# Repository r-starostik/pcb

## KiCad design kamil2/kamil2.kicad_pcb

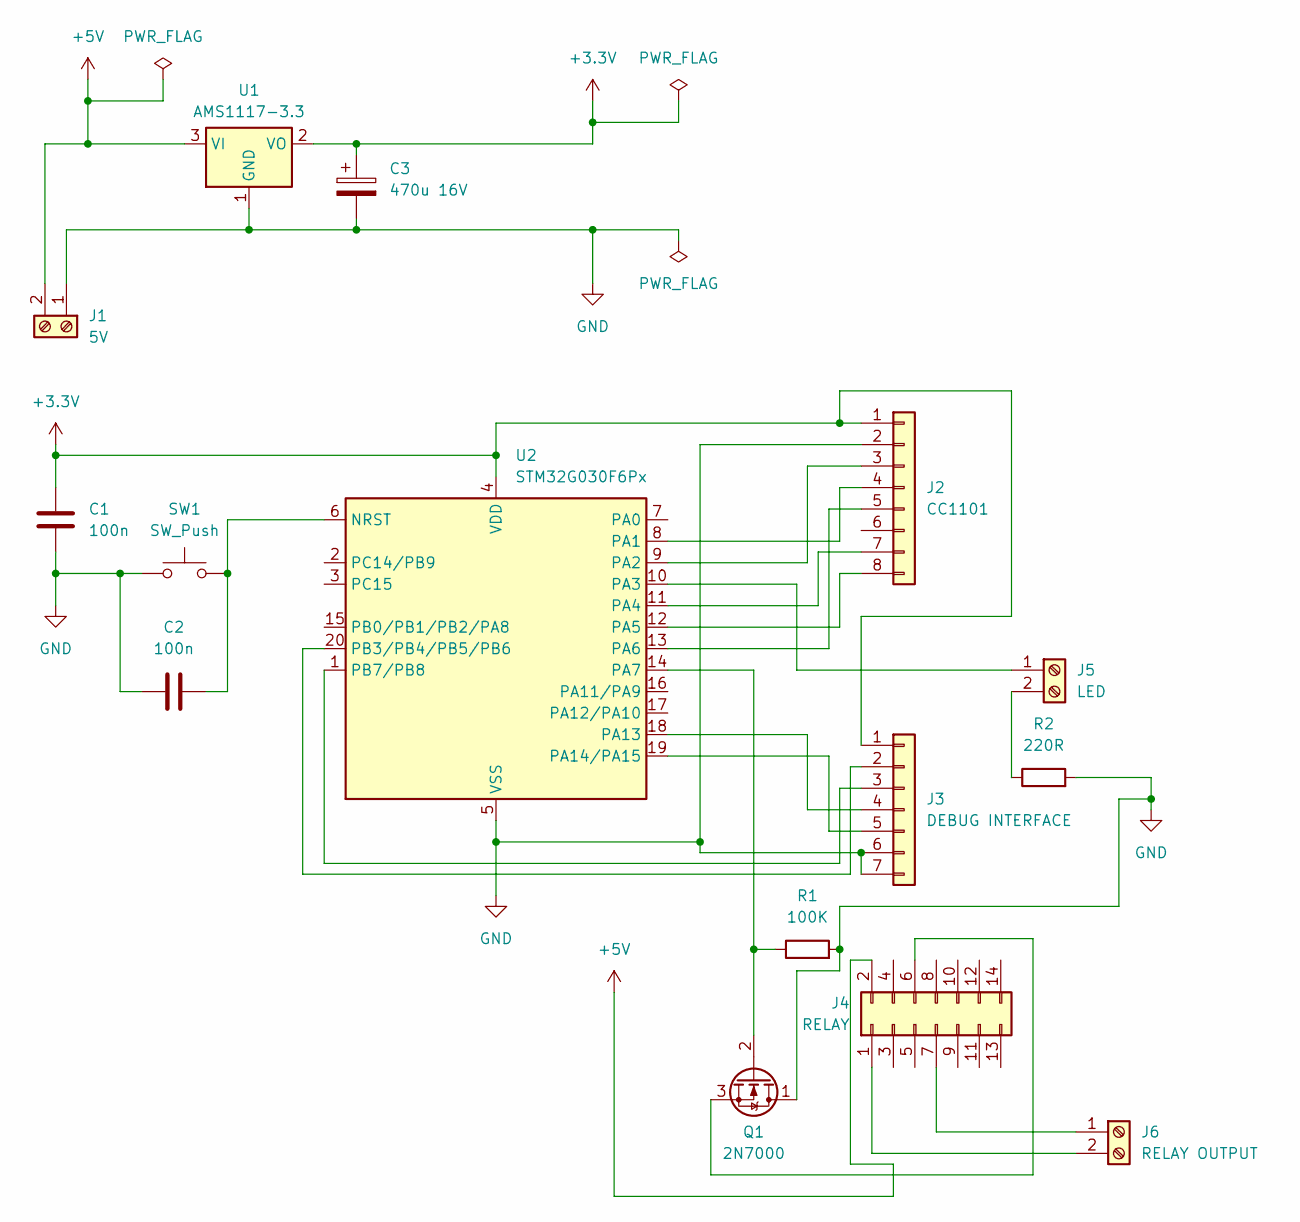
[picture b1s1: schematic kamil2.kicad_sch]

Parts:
C1, C2: 100n; C_1206_3216Metric
C3: 470u 16V; CP_Radial_D8.0mm_P3.80mm
J1: 5V; TerminalBlock_bornier-2_P5.08mm
J2: CC1101; PinSocket_1x08_P2.00mm_Vertical
J3: DEBUG INTERFACE; PinHeader_1x07_P2.54mm_Vertical
J4: RELAY; CERDIP-14_W7.62mm_SideBrazed
J5: LED; TerminalBlock_bornier-2_P5.08mm
J6: RELAY OUTPUT; TerminalBlock_bornier-2_P5.08mm
Q1: 2N7000; TO-92_Inline
R1: 100K; R_1206_3216Metric
R2: 220R; R_1206_3216Metric
SW1: SW_Push; SW_Tactile_SPST_NO_Straight_CK_PTS636Sx25SMTRLFS
U1: AMS1117-3.3; SOT-223-3_TabPin2
U2: STM32G030F6Px; TSSOP-20_4.4x6.5mm_P0.65mm

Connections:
+3.3V: C1.2, C3.1, J2.1, J3.1, U1.2 (VO), U2.4 (VDD)
+5V: J1.2, J4.2, U1.3 (VI)
GND: C1.1, C2.2, C3.2, J1.1, J2.2, J3.6, J3.7, Q1.1 (D), R1.2, R2.2, SW1.1, U1.1 (GND), U2.5 (VSS)
unnamed: J2.3, U2.9 (PA2)
unnamed: J2.4, U2.8 (PA1)
unnamed: J2.5, U2.13 (PA6)
unnamed: J2.7, U2.11 (PA4)
unnamed: J2.8, U2.12 (PA5)
unnamed: J3.2, U2.20 (PB3/PB4/PB5/PB6)
unnamed: J3.3, U2.1 (PB7/PB8)
unnamed: J3.4, U2.18 (PA13)
unnamed: J3.5, U2.19 (PA14/PA15)
unnamed: J4.1, J6.2
unnamed: J4.6, Q1.3 (S)
unnamed: J4.7, J6.1
unnamed: J5.1, U2.10 (PA3)
unnamed: J5.2, R2.1
unnamed: Q1.2 (G), R1.1, U2.14 (PA7)
unnamed: C2.1, SW1.2, U2.6 (NRST)

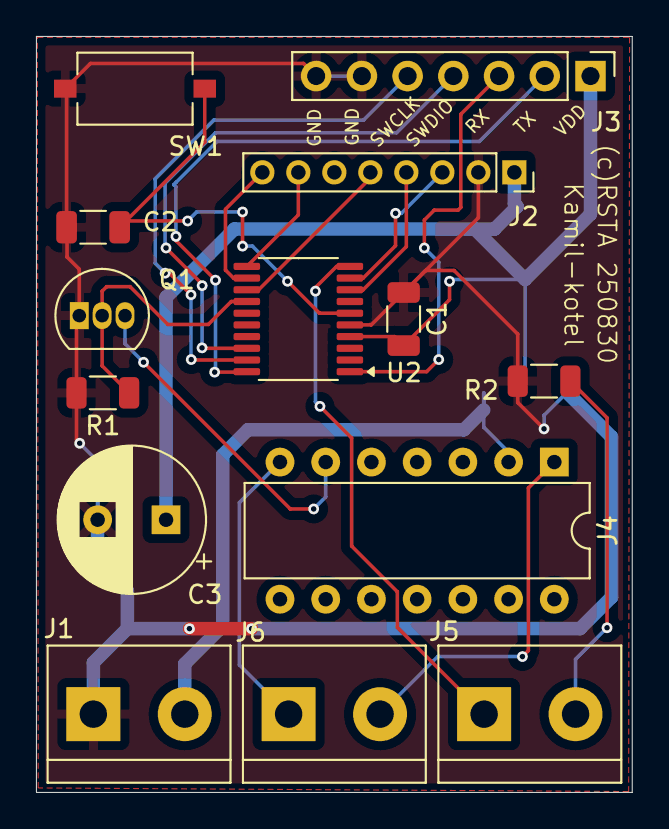
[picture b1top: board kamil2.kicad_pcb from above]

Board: 2 copper layers, 33.1 x 42.0 mm, 15 parts (1 on the bottom side), 19 nets.

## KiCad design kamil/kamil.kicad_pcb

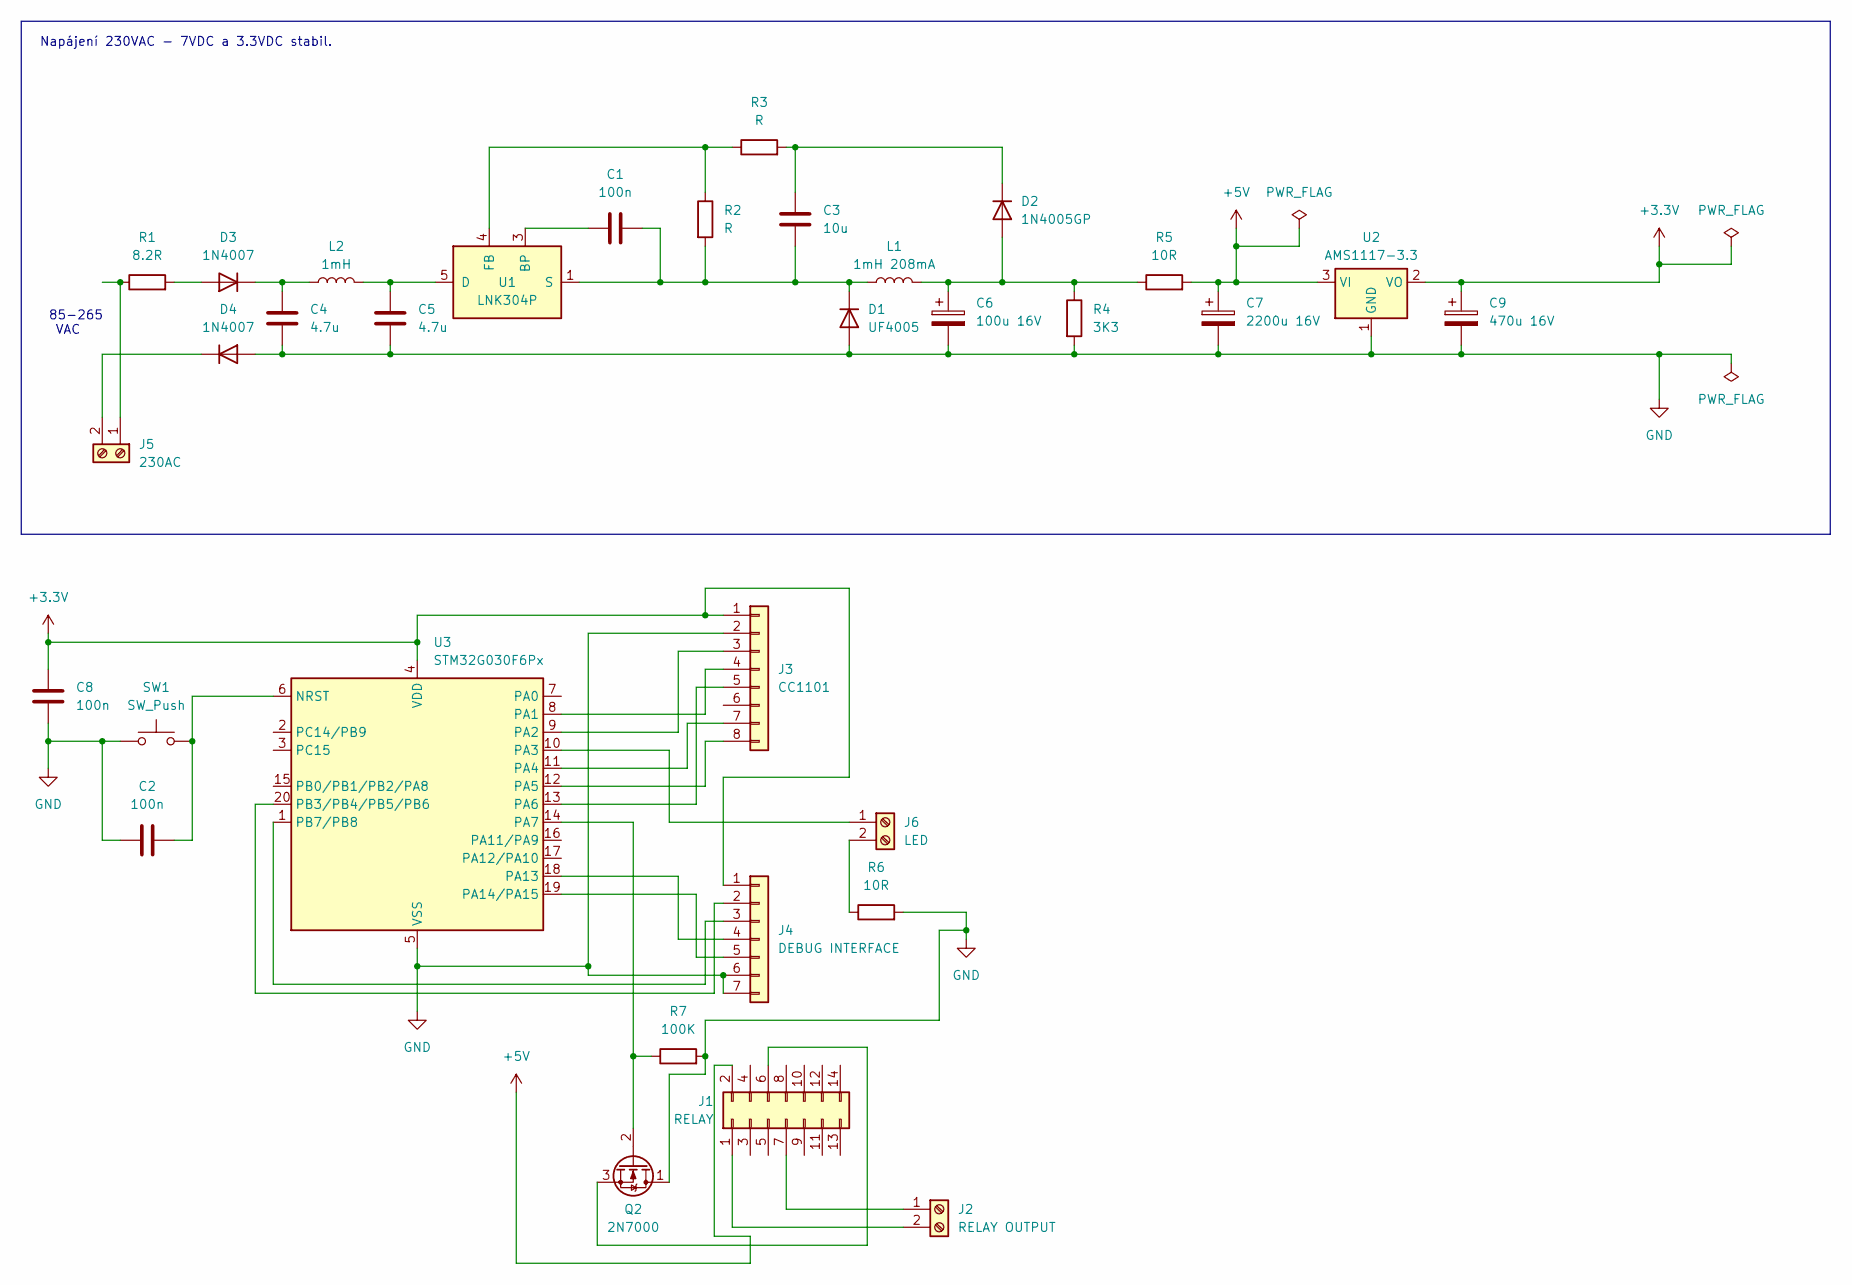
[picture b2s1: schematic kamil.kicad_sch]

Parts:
C1, C2, C8: 100n; C_1206_3216Metric
C3: 10u; CP_Radial_D5.0mm_P2.50mm
C4, C5: 4.7u; C_Rect_L29.0mm_W7.6mm_P27.50mm_MKT
C6: 100u 16V; CP_Radial_D5.0mm_P2.50mm
C7: 2200u 16V; CP_Radial_D12.5mm_P5.00mm
C9: 470u 16V; CP_Radial_D8.0mm_P3.80mm
D1: UF4005; D_DO-41_SOD81_P10.16mm_Horizontal
D2: 1N4005GP; D_DO-41_SOD81_P10.16mm_Horizontal
D3, D4: 1N4007; D_DO-41_SOD81_P10.16mm_Horizontal
J1: RELAY; CERDIP-14_W7.62mm_SideBrazed
J2: RELAY OUTPUT; TerminalBlock_bornier-2_P5.08mm
J3: CC1101; PinSocket_1x08_P2.00mm_Vertical
J4: DEBUG INTERFACE; PinHeader_1x07_P2.54mm_Vertical
J5: 230AC; TerminalBlock_bornier-2_P5.08mm
J6: LED; TerminalBlock_bornier-2_P5.08mm
L1: 1mH 208mA; L_Radial_D10.5mm_P5.00mm_Abacron_AISR-01
L2: 1mH; L_Radial_D10.5mm_P5.00mm_Abacron_AISR-01
Q2: 2N7000; TO-92_Inline
R1: 8.2R; R_Axial_DIN0414_L11.9mm_D4.5mm_P15.24mm_Horizontal
R2, R3: R; R_1206_3216Metric
R4: 3K3; R_1206_3216Metric
R5, R6: 10R; R_1206_3216Metric
R7: 100K; R_1206_3216Metric
SW1: SW_Push; SW_Tactile_SPST_NO_Straight_CK_PTS636Sx25SMTRLFS
U1: LNK304P; PowerIntegrations_PDIP-8B
U2: AMS1117-3.3; SOT-223-3_TabPin2
U3: STM32G030F6Px; TSSOP-20_4.4x6.5mm_P0.65mm

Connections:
+3.3V: C8.2, C9.1, J3.1, J4.1, U2.2 (VO), U3.4 (VDD)
+5V: C7.1, J1.2, R5.2, U2.3 (VI)
GND: C2.2, C4.2, C5.2, C6.2, C7.2, C8.1, C9.2, D1.2 (A), D4.2 (A), J3.2, J4.6, J4.7, Q2.1 (D), R4.2, R6.2, R7.2, SW1.1, U2.1 (GND), U3.5 (VSS)
unnamed: C1.2, C3.2, D1.1 (K), L1.1, R2.2, U1.1 (S), U1.2 (S), U1.7 (S), U1.8 (S)
unnamed: C6.1, D2.2 (A), L1.2, R4.1, R5.1
unnamed: C3.1, D2.1 (K), R3.2
unnamed: D3.2 (A), R1.2
unnamed: C4.1, D3.1 (K), L2.1
unnamed: D4.1 (K), J5.2
unnamed: J1.1, J2.2
unnamed: J1.6, Q2.3 (S)
unnamed: J1.7, J2.1
unnamed: J3.3, U3.9 (PA2)
unnamed: J3.4, U3.8 (PA1)
unnamed: J3.5, U3.13 (PA6)
unnamed: J3.7, U3.11 (PA4)
unnamed: J3.8, U3.12 (PA5)
unnamed: J4.2, U3.20 (PB3/PB4/PB5/PB6)
unnamed: J4.3, U3.1 (PB7/PB8)
unnamed: J4.4, U3.18 (PA13)
unnamed: J4.5, U3.19 (PA14/PA15)
unnamed: J5.1, R1.1
unnamed: J6.1, U3.10 (PA3)
unnamed: J6.2, R6.1
unnamed: Q2.2 (G), R7.1, U3.14 (PA7)
unnamed: C1.1, U1.3 (BP)
unnamed: C5.1, L2.2, U1.5 (D)
unnamed: R2.1, R3.1, U1.4 (FB)
unnamed: C2.1, SW1.2, U3.6 (NRST)

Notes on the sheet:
Napájení 230VAC - 7VDC a 3.3VDC stabil.
85-265 VAC

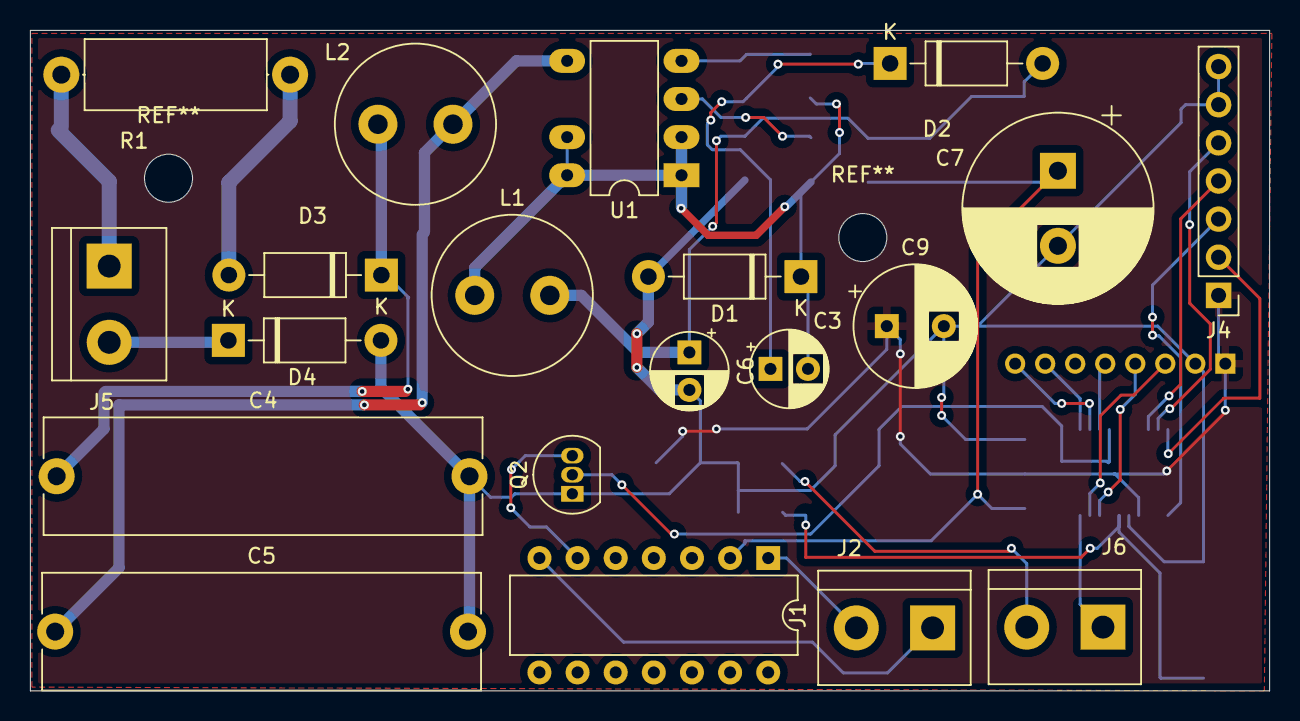
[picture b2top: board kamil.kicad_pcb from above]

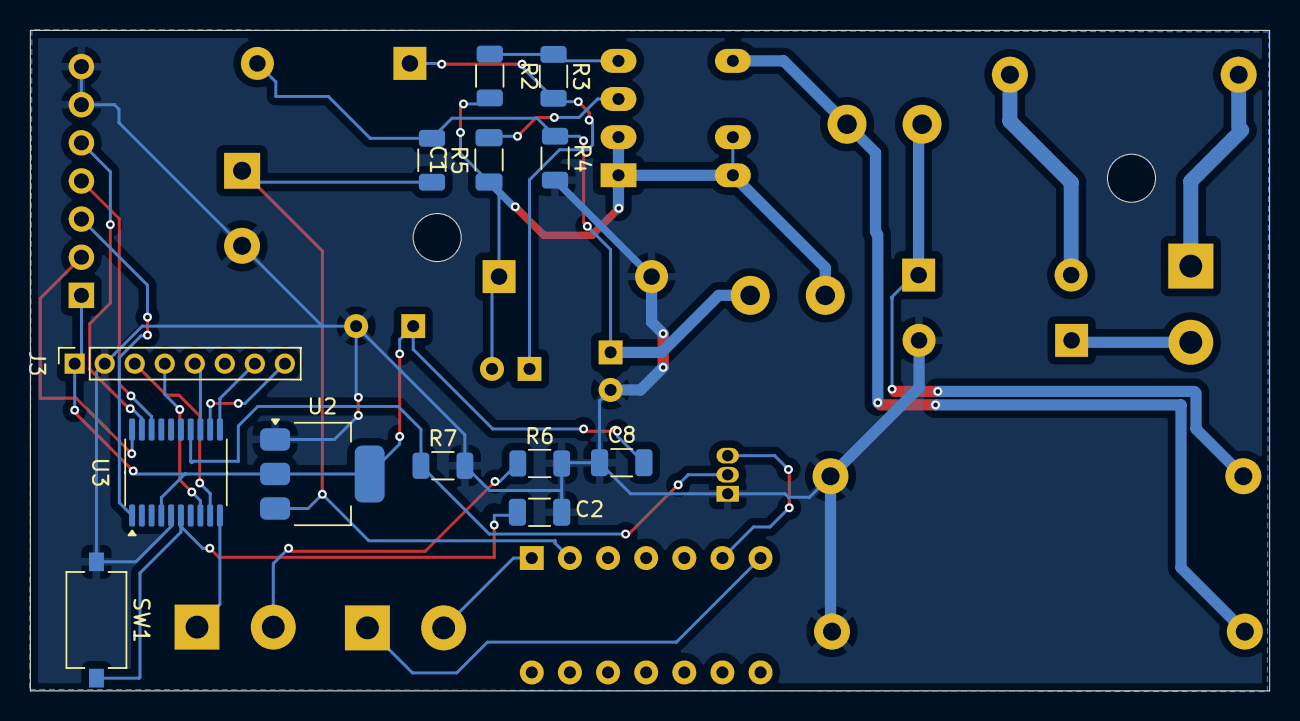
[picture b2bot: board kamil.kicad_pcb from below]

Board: 2 copper layers, 82.5 x 44.0 mm, 33 parts (13 on the bottom side), 29 nets.

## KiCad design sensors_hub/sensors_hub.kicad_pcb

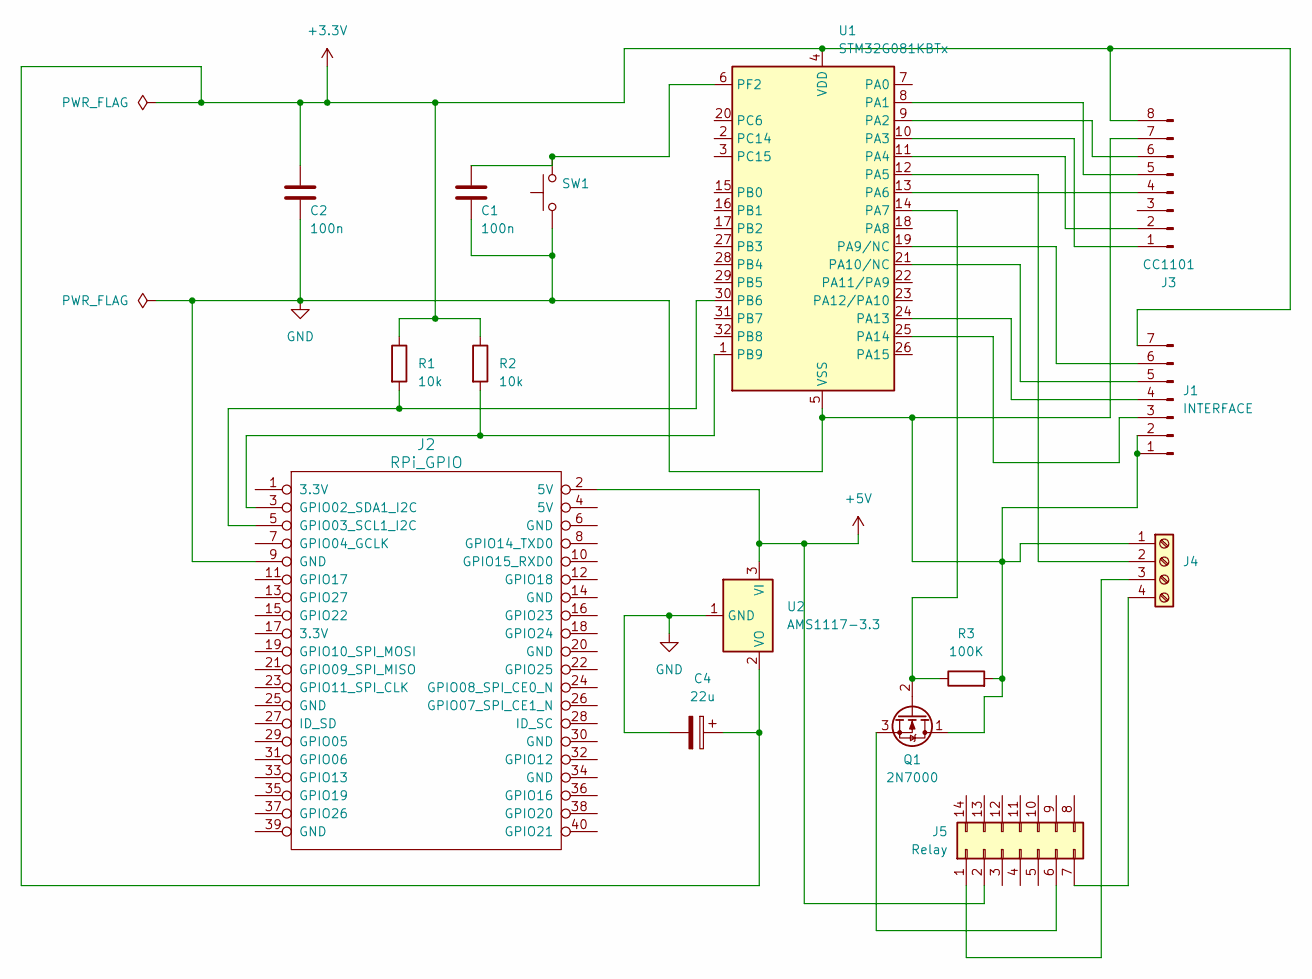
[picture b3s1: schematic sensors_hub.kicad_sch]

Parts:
C1: 100n; R_1206_3216Metric
C2: 100n; C_1206_3216Metric
C4: 22u; CP_Radial_D5.0mm_P2.00mm
J1: INTERFACE; PinHeader_1x07_P2.54mm_Vertical
J2: RPi_GPIO; PinSocket_2x20_P2.54mm_Vertical
J3: CC1101; PinSocket_1x08_P2.00mm_Vertical
J4: TerminalBlock_bornier-4_P5.08mm
J5: Relay; CERDIP-14_W7.62mm_SideBrazed
Q1: 2N7000; TO-92_Inline
R1, R2: 10k; R_1206_3216Metric
R3: 100K; R_1206_3216Metric
SW1: SW_Push; SW_Tactile_SPST_NO_Straight_CK_PTS636Sx25SMTRLFS
U1: STM32G081KBTx; LQFP-32_7x7mm_P0.8mm
U2: AMS1117-3.3; SOT-223-3_TabPin2

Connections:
+3.3V: C2.1, C4.1, J1.7, J3.8, R1.1, R2.1, U1.4 (VDD), U2.2 (VO)
+5V: J2.2 (5V), J5.2, U2.3 (VI)
GND: C1.2, C2.2, C4.2, J1.1, J1.2, J2.9 (GND), J3.7, J4.1, Q1.1 (D), R3.2, SW1.1, U1.5 (VSS), U2.1 (GND)
unnamed: J1.3, U1.25 (PA14)
unnamed: J1.4, U1.24 (PA13)
unnamed: J1.5, U1.21 (PA10/NC)
unnamed: J1.6, U1.19 (PA9/NC)
unnamed: J2.3 (GPIO02_SDA1_I2C), R2.2, U1.1 (PB9)
unnamed: J2.5 (GPIO03_SCL1_I2C), R1.2, U1.30 (PB6)
unnamed: J3.1, U1.10 (PA3)
unnamed: J3.2, U1.11 (PA4)
unnamed: J3.4, U1.13 (PA6)
unnamed: J3.5, U1.8 (PA1)
unnamed: J3.6, U1.9 (PA2)
unnamed: J4.2, U1.12 (PA5)
unnamed: J4.3, J5.1
unnamed: J4.4, J5.7
unnamed: J5.6, Q1.3 (S)
unnamed: Q1.2 (G), R3.1, U1.14 (PA7)
unnamed: C1.1, SW1.2, U1.6 (PF2)

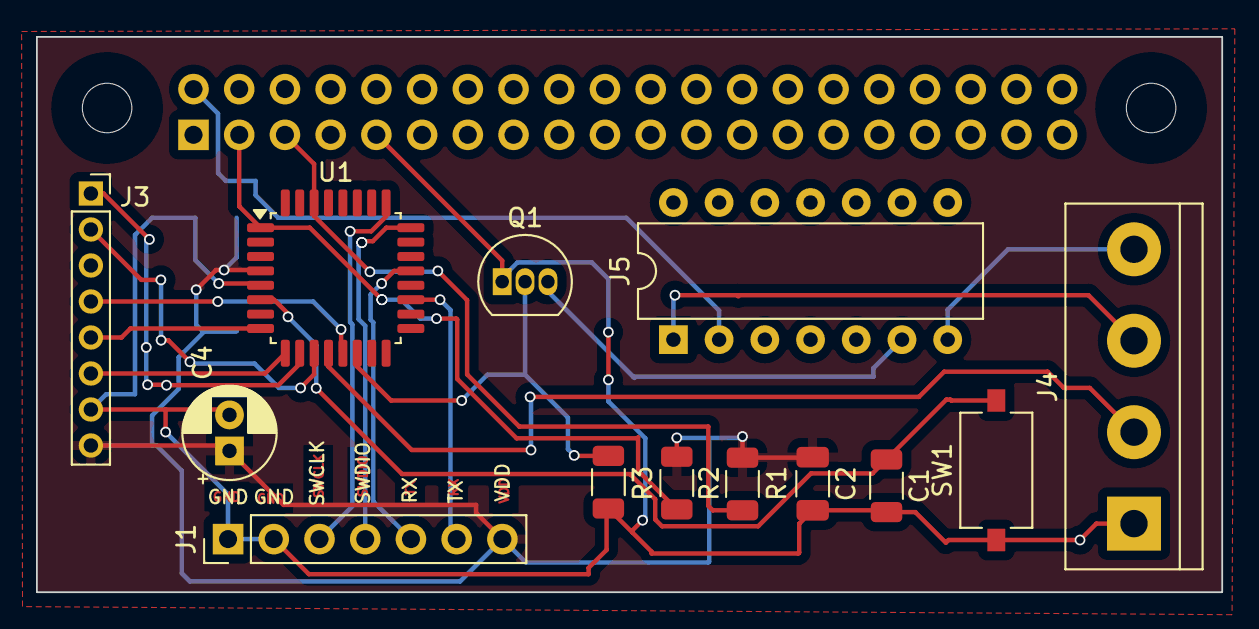
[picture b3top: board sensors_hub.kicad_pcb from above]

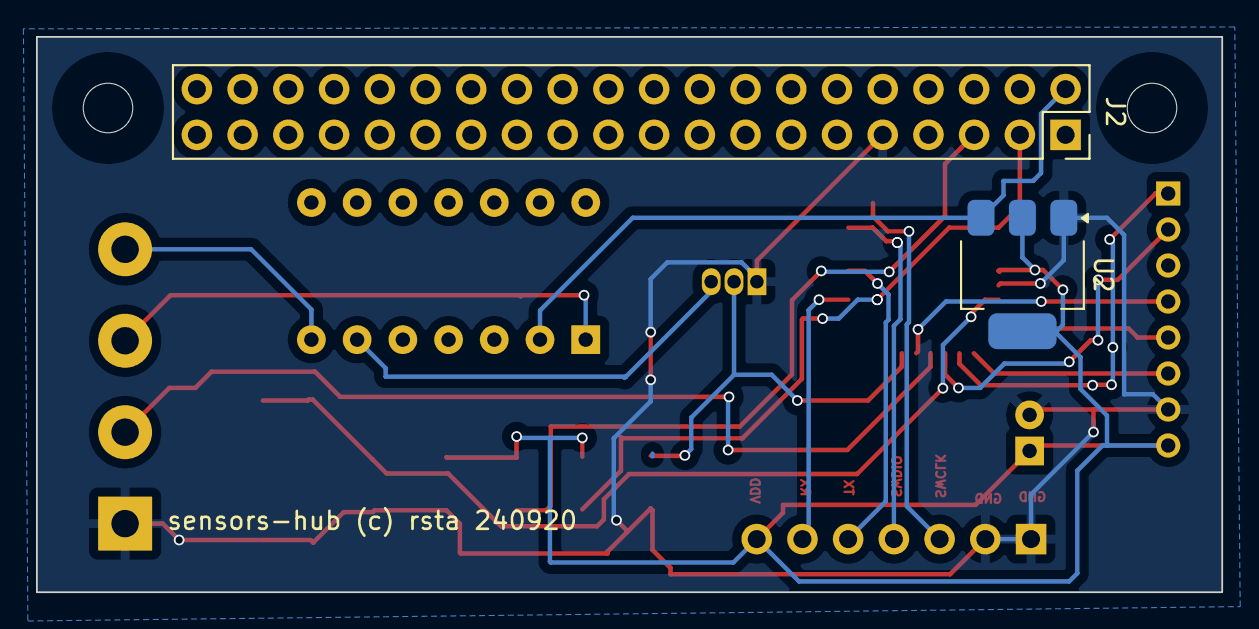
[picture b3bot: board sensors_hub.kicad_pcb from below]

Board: 2 copper layers, 65.9 x 30.8 mm, 15 parts (2 on the bottom side), 20 nets.

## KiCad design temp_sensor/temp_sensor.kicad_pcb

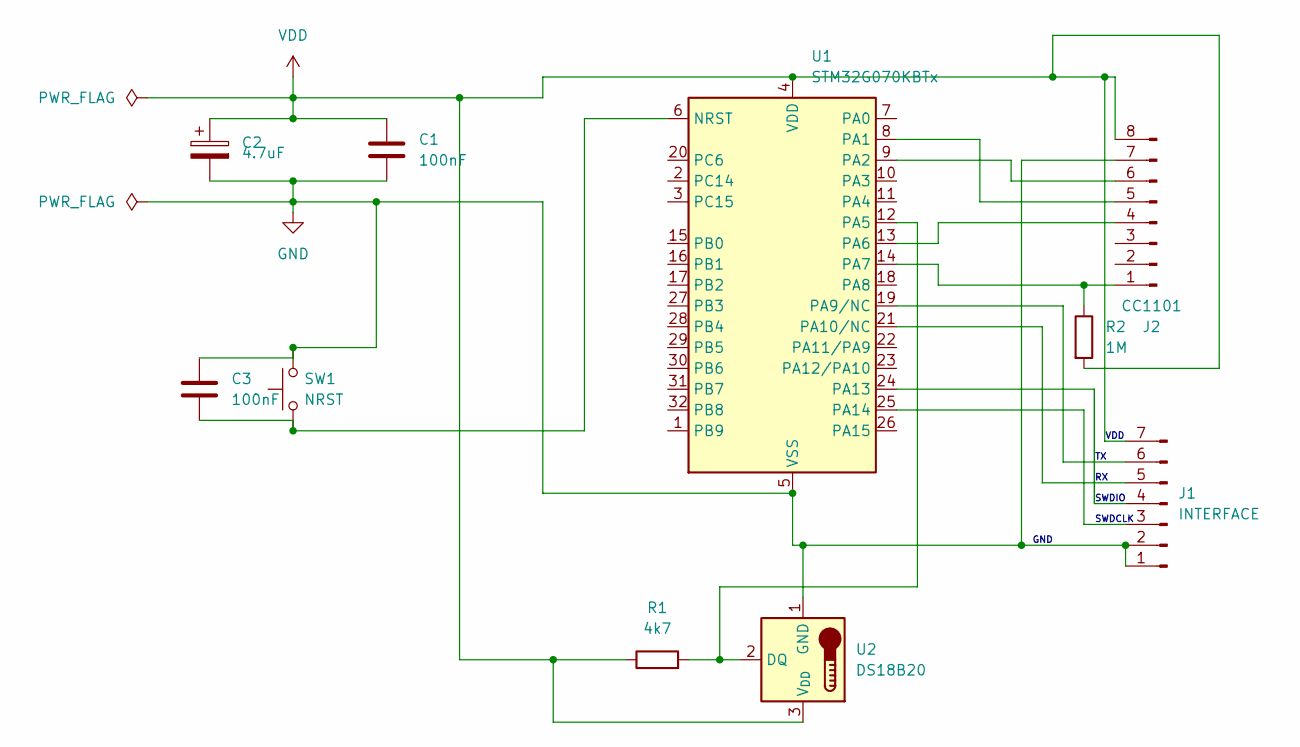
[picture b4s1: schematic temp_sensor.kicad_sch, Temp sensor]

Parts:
C1, C3: 100nF; C_1206_3216Metric
C2: 4.7uF; CP_Radial_D4.0mm_P2.00mm
J1: INTERFACE; PinHeader_1x07_P2.54mm_Vertical
J2: CC1101; PinSocket_1x08_P2.00mm_Vertical
R1: 4k7; R_1206_3216Metric
R2: 1M; R_1206_3216Metric
SW1: NRST; SW_Tactile_SPST_NO_Straight_CK_PTS636Sx25SMTRLFS
U1: STM32G070KBTx; LQFP-32_7x7mm_P0.8mm
U2: DS18B20; TO-92_Inline

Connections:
GND: C1.2, C2.2, C3.1, J1.1, J1.2, J2.7, SW1.2, U1.5 (VSS), U2.1 (GND)
unnamed: J1.3, U1.25 (PA14)
unnamed: J1.4, U1.24 (PA13)
unnamed: J1.5, U1.21 (PA10/NC)
unnamed: J1.6, U1.19 (PA9/NC)
unnamed: J2.1, R2.1, U1.14 (PA7)
unnamed: J2.4, U1.13 (PA6)
unnamed: J2.5, U1.8 (PA1)
unnamed: J2.6, U1.9 (PA2)
unnamed: C3.2, SW1.1, U1.6 (NRST)
unnamed: R1.2, U1.12 (PA5), U2.2 (DQ)
VDD: C1.1, C2.1, J1.7, J2.8, R1.1, R2.2, U1.4 (VDD), U2.3 (V_{DD})

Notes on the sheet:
GND
VDD
SWDIO
SWDCLK

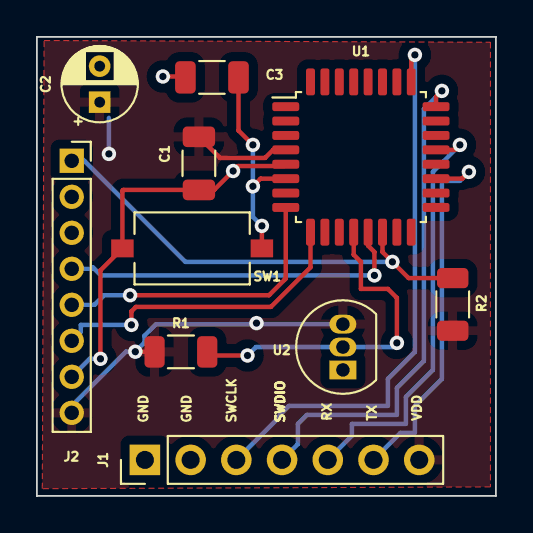
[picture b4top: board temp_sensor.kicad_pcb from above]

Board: 2 copper layers, 25.5 x 25.5 mm, 10 parts (0 on the bottom side), 12 nets.

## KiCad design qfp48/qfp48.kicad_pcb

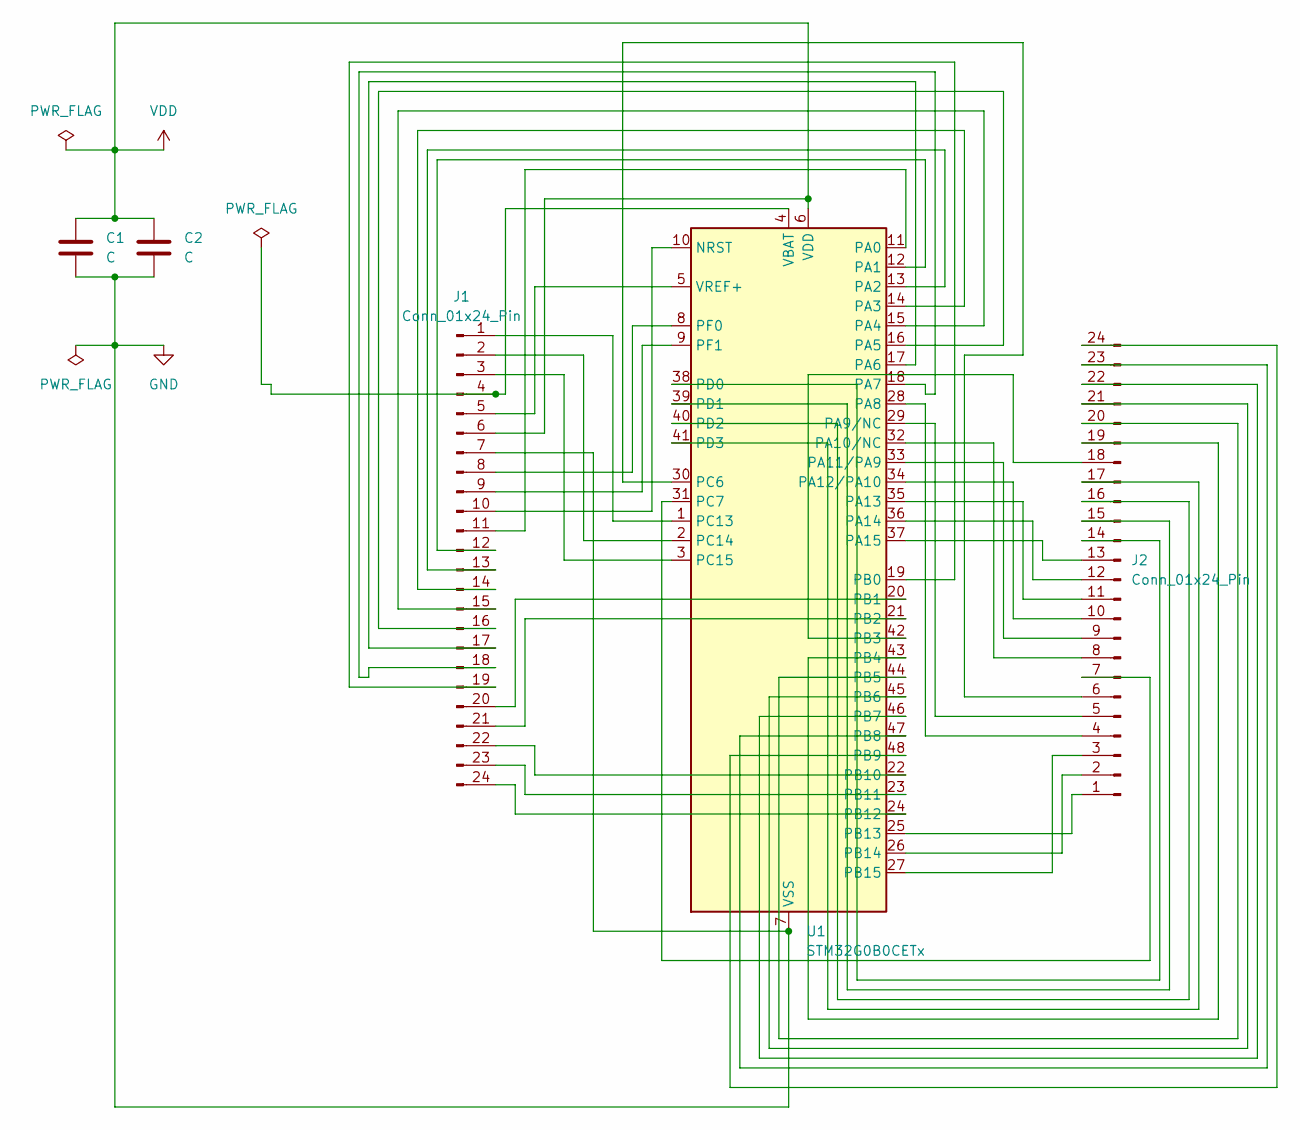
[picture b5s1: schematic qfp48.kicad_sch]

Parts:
C1, C2: C; C_1206_3216Metric
J1, J2: Conn_01x24_Pin; PinHeader_1x24_P2.54mm_Vertical
U1: STM32G0B0CETx; LQFP-48_7x7mm_P0.5mm

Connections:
GND: C1.2, C2.2, J1.7, U1.7 (VSS)
unnamed: J1.1, U1.1 (PC13)
unnamed: J1.2, U1.2 (PC14)
unnamed: J1.3, U1.3 (PC15)
unnamed: J1.4, U1.4 (VBAT)
unnamed: J1.5, U1.5 (VREF+)
unnamed: J1.8, U1.8 (PF0)
unnamed: J1.9, U1.9 (PF1)
unnamed: J1.10, U1.10 (NRST)
unnamed: J1.11, U1.11 (PA0)
unnamed: J1.12, U1.12 (PA1)
unnamed: J1.13, U1.13 (PA2)
unnamed: J1.14, U1.14 (PA3)
unnamed: J1.15, U1.15 (PA4)
unnamed: J1.16, U1.16 (PA5)
unnamed: J1.17, U1.17 (PA6)
unnamed: J1.18, U1.18 (PA7)
unnamed: J1.19, U1.19 (PB0)
unnamed: J1.20, U1.20 (PB1)
unnamed: J1.21, U1.21 (PB2)
unnamed: J1.22, U1.22 (PB10)
unnamed: J1.23, U1.23 (PB11)
unnamed: J1.24, U1.24 (PB12)
unnamed: J2.1, U1.25 (PB13)
unnamed: J2.2, U1.26 (PB14)
unnamed: J2.3, U1.27 (PB15)
unnamed: J2.4, U1.28 (PA8)
unnamed: J2.5, U1.29 (PA9/NC)
unnamed: J2.6, U1.30 (PC6)
unnamed: J2.7, U1.31 (PC7)
unnamed: J2.8, U1.32 (PA10/NC)
unnamed: J2.9, U1.33 (PA11/PA9)
unnamed: J2.10, U1.34 (PA12/PA10)
unnamed: J2.11, U1.35 (PA13)
unnamed: J2.12, U1.36 (PA14)
unnamed: J2.13, U1.37 (PA15)
unnamed: J2.14, U1.38 (PD0)
unnamed: J2.15, U1.39 (PD1)
unnamed: J2.16, U1.40 (PD2)
unnamed: J2.17, U1.41 (PD3)
unnamed: J2.18, U1.42 (PB3)
unnamed: J2.19, U1.43 (PB4)
unnamed: J2.20, U1.44 (PB5)
unnamed: J2.21, U1.45 (PB6)
unnamed: J2.22, U1.46 (PB7)
unnamed: J2.23, U1.47 (PB8)
unnamed: J2.24, U1.48 (PB9)
VDD: C1.1, C2.1, J1.6, U1.6 (VDD)

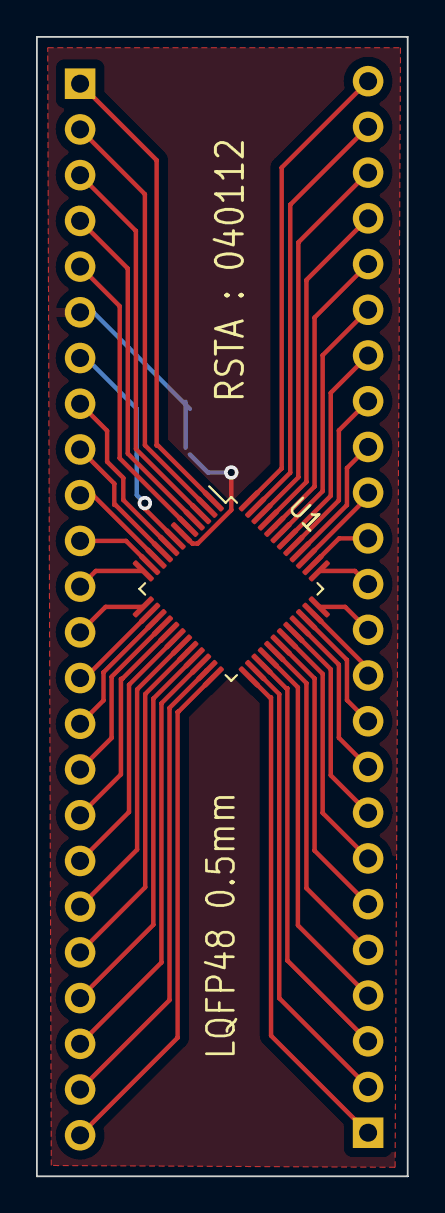
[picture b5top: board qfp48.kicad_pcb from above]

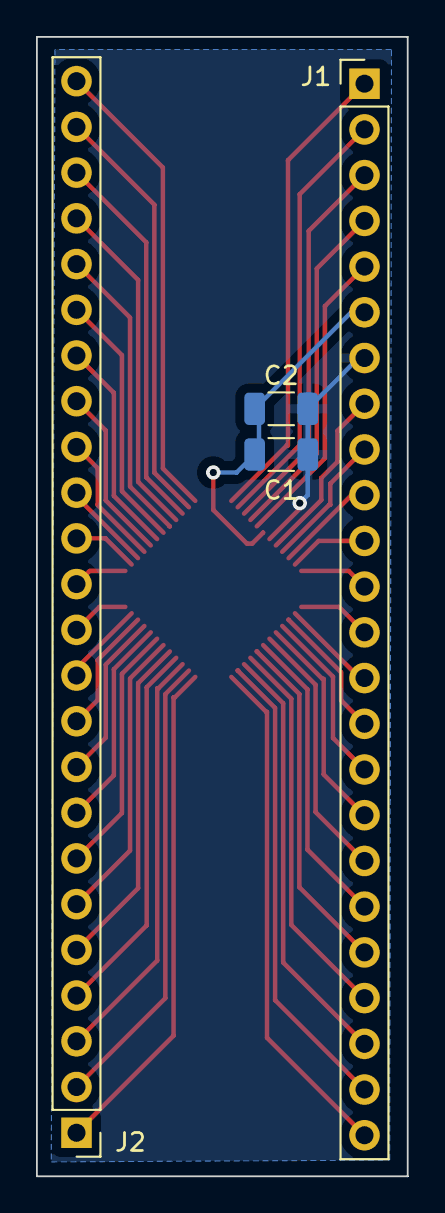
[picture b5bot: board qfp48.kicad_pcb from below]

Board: 2 copper layers, 20.6 x 63.3 mm, 5 parts (4 on the bottom side), 48 nets.

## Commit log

2024-01-02 init
2024-01-12 Finish - order in PCBWAY
2024-03-09 Cleaning
2024-03-09 Refactor
2024-09-14 sensors_hub
2025-08-09 kamil
2025-08-09 Kamil...
2025-08-18 To be continued.
2025-08-19 Implementation
2025-08-30 kami2
